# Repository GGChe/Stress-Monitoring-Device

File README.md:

# Welcome to FreeStressGame's open source Project!

Our tream provides an open-source real time embedded project based on the development of a real time biomedical device which aim is to monitor the stress level of a videogame player. This project is open source and anyone is invited to contribute freely sharing all your tips and modifications

## Table of Contents

* [Introduction](#introduction)
* [Methodology](#methodology)
* [Required Components](#required-components)
* [System Manual](#system-manual)
* [Found a Bug](#found-a-bug)
* [Contributing](#contributing)
* [Pubilcation](#publication)
* [SNS](#sns)
* [License](#lisence)

### Introduction

According to the World Health Organisation, mental disorders are a main topic in global health, specially because one in four people in the world will be affected by mental or neurological disorders at some point in their lives. It is estimated that more that 450 million people are currently suffering from such disorders, placing this risk to the top of all the ill-health's causes and disability worldwide. The main mental disorder is depression, and in many situations it is caused by stress. Nowadays, stress is a risk that every person need to face in some point of the day, like work, house, friends, etc. 

There is evidence available that supports the fact that the stress is one of the main triggers of depression. More in detail , such evidence shows that depression can stem from chronic overstimulation of the body's hypothalamic-pituitary-adrenal axis, which produces cortisol in humans. However, while adults can face the stress with therapy and different skills, children are a very enthreaten sector of the population that does not own skills against that. 

With the mentioned before, we can imagine that one of the most risky situations for a child are videogames where we set an unprepared person against a stressfull and addictive situation, causing severe damage on the child. 

Then, this project constitutes a reliable and attractive solution for parents, therapists and adults that want to monitor and control the stress status of the player.

### Methodology
#### [HeartBeat Detection]
The heartbeat measurement technology that we chose for this project is the photopletismography. 
This technique is based on the use of a photodiodethat emits a light pulse in a specific wavelength which, after passing by the blood vessel, the wavelength signal captured by the photosensor changes.  

</img>

According to that change, we can determine whether a pulse of blood has passed in a specific time, depending on our sampling rate.  

#### [Stress Recognition] 
Once the signal is taken, it is carried to the raspberry Pi using a proper wirebased connection to avoid any unwanted interaction with other signals and for a better performance of the device.  
Then, the Raspberry PI will process the data in real time and, at the same time, it will do a basic threshold based control for deciding whether the person is under stress or not. When this process recognize the stress, it makes beep sound for warning. 

### Required Components 
The device consists of the next components:
- Raspberry Pi 3 B+
- PCB adaptor: 
  * 2 X 2Kohm SMD resistors
- Wrist sensor:
  * VEML6030 Light sensor 
  * 1 X IR LED
  * 1 X 1 Kohm SMD resistor 
  * 1 X 10 Kohm SMD resistor
  * 1 X 1000 nF SMD capasitor 
- Piezo Buzzer
- RJ45 Cable
- Finger / Band type case for Wrist sensor
- Raspberry Pi case 

All circuit schematics / PCB Eagle files/ 3D Solidworks files are included in UPLOADED DOCUMENTS. 

### System Description 

#### Hardware section 
In this section you will find useful information of how to replicate our project. Given the components listed before, you need to print the pcb, which files and more deep information is shown in the PCB folder.  

</img>

* Connect PCB adaptor with Wrist sensor by RJ45 cable
* Connect PCB adaptor pins with Raspberry Pi pins as shown in below table 

<p align="center">

<p align="center">

#### Software section

##### Software setting 
To build our program in your Pi, you need to follow some steps.  

```
sudo apt-get update

git clone https://github.com/GGChe/Stress_Controller_Device
```
You would need to update and install the libraries of PHP5.6, Apache2 and compilers if your are working on a vanilla version of the OS.

```
sudo apt-get install php5.6

sudo apt-get install apache2

sudo apt-get install g++
```
If you have any problem installing php5.6 in Raspbian, cause it is not very well supported, follow this guide:
https://unnikked.ga/how-to-install-php-5-6-on-a-raspberry-pi-2-5fd93879cb14

##### Driver 
We developed a driver for the VEML6030 sensor, that uses I2C communication protocol, using the data obtained from the link below. The driver given in that project was initially prepared for Arduino but we had to modify it completely to make it run in every system using a proper c++ code.

[Mbed VEML6030 Driver](https://os.mbed.com/teams/MSS/code/VEML6030/)

##### Compilation from source

To compile the whole code, you only need to go to the code's folder and type on the terminal

```
cmake .

make 

sudo ./StressC.out
```

To run the program from the boot of the system

```
sudo nano /etc/rc.local

```

And then, write before "exit 0" the following scrypt:

```
sudo ./PATH/StressC.out

```

### Found a bug?

Bugs can be reported at: https://github.com/GGChe/Stress_Controller_Device/issues

Please try the latest release build before reporting, be sure to also include any logs or steps to reproduce you may have, as well as your Forge version, and whether or not you are using a third party loader such as Cauldron. When submitting logs please use a service such as Pastebin, do not paste the log directly into the issue.

### Contributing

Ahmed Elmogamer 
* Main role: Software Engineer 
* Specific tasks 
  : Coding the main program and making sensors' driver.  

Daewon Jung  
* Main role: Mechanical Engineer 
* Specific tasks 
  : Designing cases, assist making PCB and Promotion. 
  
Gabriel Galeote Checa 
* Main role: Electronic Engineer 
* Specific tasks 
  : Designing PCB and Website architecture development, Fabrication and Soldering of the PCB. 
  
### Publication
Check our publication in Hackaday.

### SNS 
In our socialmedia you can find some demos and video explanations of how the system works. 

Check our two youtube videos explaining how the system works!
- https://www.youtube.com/watch?v=JRjO4hhqV6E
- https://www.youtube.com/watch?v=9uvpTM_b6e0&t=2s
### Credits

This project used the current driver uploaded in mbed for other purposes, we fixed some errors for the VEML6030 use in RPI and we had to recode some sections of the driver.

We also wannt to thanks our mate Cheng who was really helpful in the lab.

### License

The MIT License

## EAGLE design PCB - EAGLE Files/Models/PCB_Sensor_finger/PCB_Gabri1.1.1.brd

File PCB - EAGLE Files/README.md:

# Electronic Design

This project consists of 2 main Printec Circuit Boards (PCB)pcbs: RPI adaptor and Sensor PCb.

The feature of the RPI adaptor pcb is to connect the correct RPI pines to the sensor circuit that we are using. We need to guide all the signal through a RJ45 cable that is going to the sensor pcb. Thus, it is need to adapt and guide signal in the correct order. 

The pcbs are shown below:
<p align="center">

<p align="center">

All the components that we are using on the PCB are Surface Mount Devices (SMD) and therefore, we should need a reflow oven to solder them, even though youu can solder everything by hang if you are skilled enough.

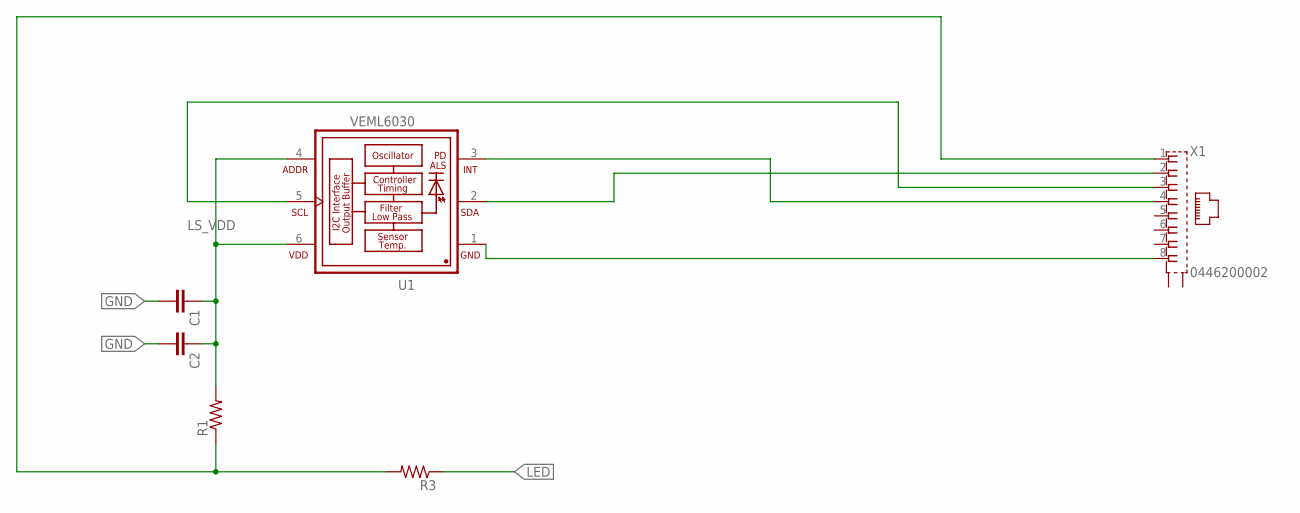
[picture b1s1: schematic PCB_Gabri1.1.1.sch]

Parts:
C1, C2: C-EU025-024X044; C025-024X044
R1, R3: R-US_R0805; R0805
U1: VEML6030; VISHAY_VEML6030_2X2X0.87
X1: 0446200002

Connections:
3V3: R1.1, R3.2, X1.1
GND: C1.2, C2.2, U1.1 (GND), X1.8
INT: U1.3 (INT), X1.4
LED: R3.1
LS_VDD: C1.1, C2.1, R1.2, U1.4 (ADDR), U1.6 (VDD)
SCL: U1.5 (SCL), X1.3
SDA: U1.2 (SDA), X1.2

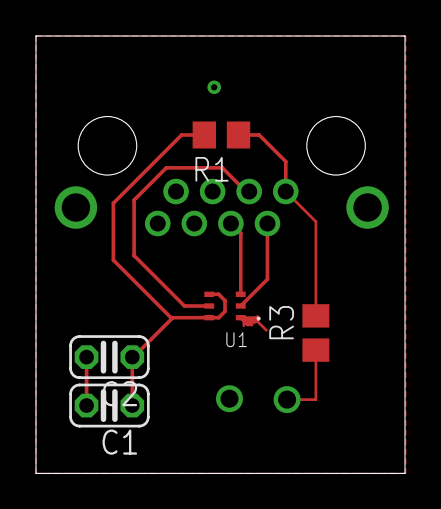
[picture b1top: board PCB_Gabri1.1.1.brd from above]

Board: 2 copper layers, 20.5 x 24.3 mm, 6 parts (1 on the bottom side), 6 nets.

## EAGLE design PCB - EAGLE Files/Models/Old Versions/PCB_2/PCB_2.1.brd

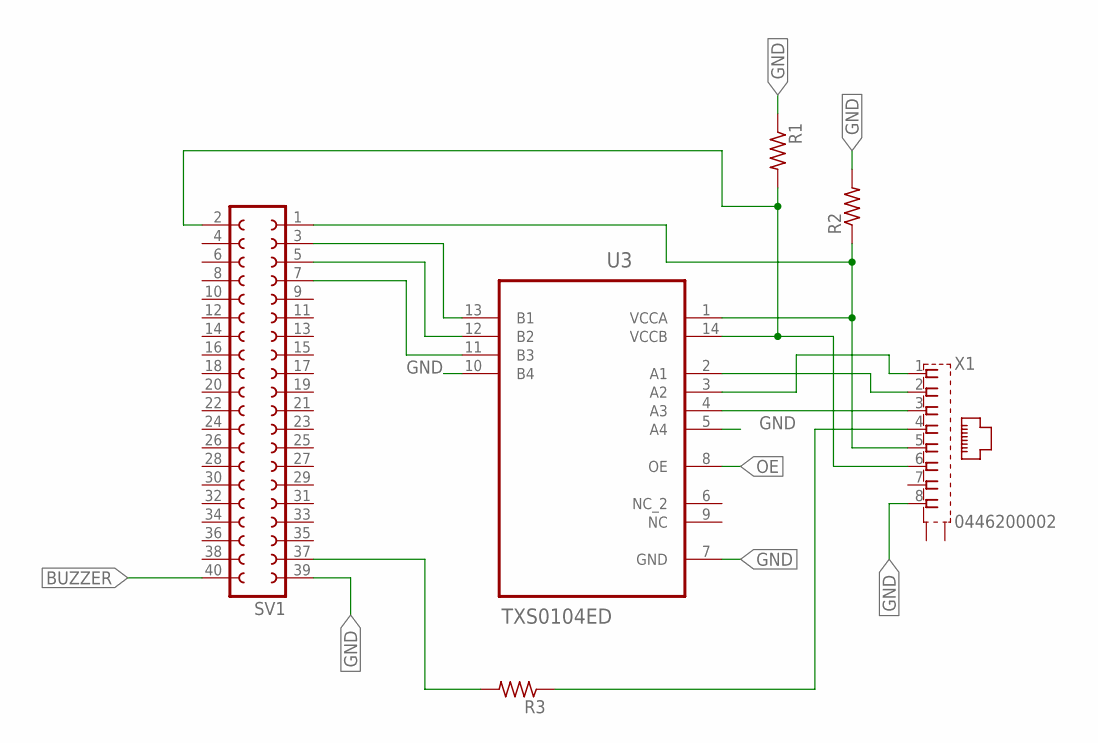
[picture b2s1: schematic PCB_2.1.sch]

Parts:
R1, R2, R3: R-US_R0805; R0805
SV1: FE20-2
U3: TXS0104ED; SOIC127P600X175-14N
X1: 0446200002

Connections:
A1: U3.2 (A1), X1.2
A2: U3.3 (A2), X1.1
A3: U3.4 (A3), X1.3
BUZZER: SV1.40
GND: R1.1, R2.2, SV1.39, U3.5 (A4), U3.7 (GND), U3.10 (B4), X1.8
INT: SV1.7, U3.11 (B3)
LED: R3.1, X1.4
unnamed: R3.2, SV1.37
OE: U3.8 (OE)
SCL: SV1.5, U3.12 (B2)
SDA: SV1.3, U3.13 (B1)
VCCA: R2.1, SV1.1, U3.1 (VCCA), X1.5
VCCB: R1.2, SV1.2, U3.14 (VCCB), X1.6

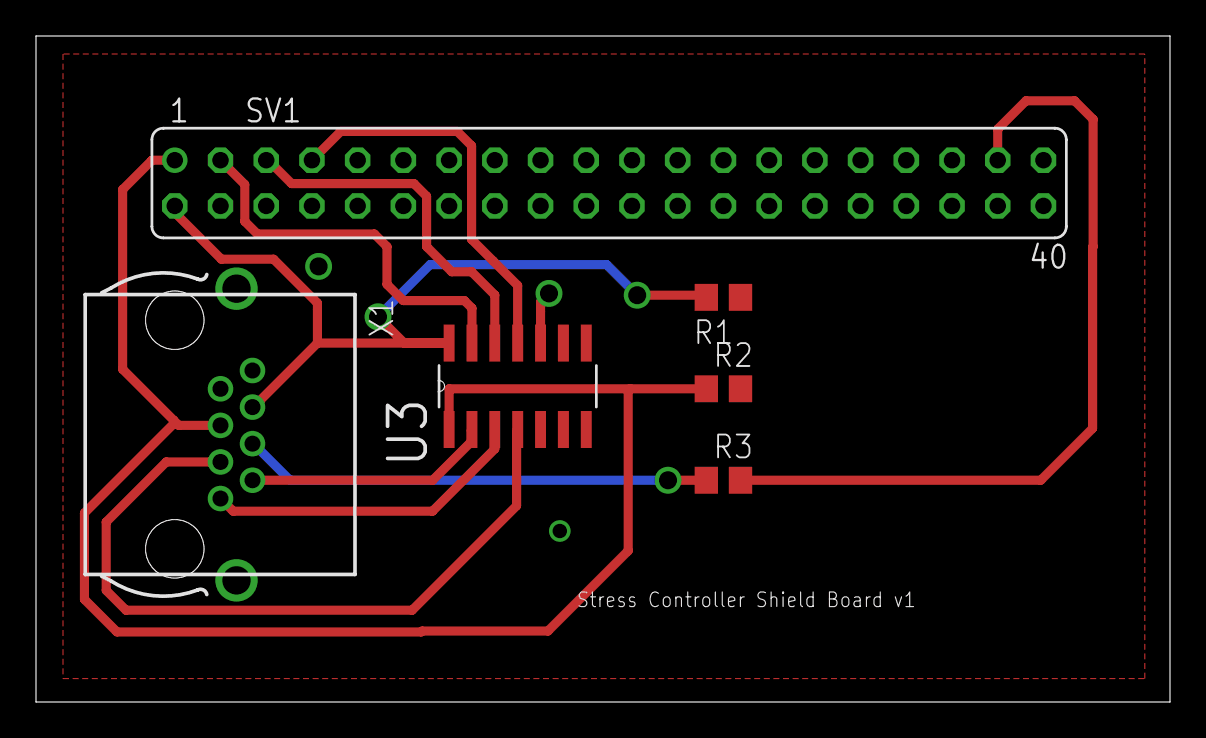
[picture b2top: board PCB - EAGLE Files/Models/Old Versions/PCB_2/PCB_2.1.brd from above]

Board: 2 copper layers, 63.0 x 37.0 mm, 6 parts (0 on the bottom side), 11 nets.

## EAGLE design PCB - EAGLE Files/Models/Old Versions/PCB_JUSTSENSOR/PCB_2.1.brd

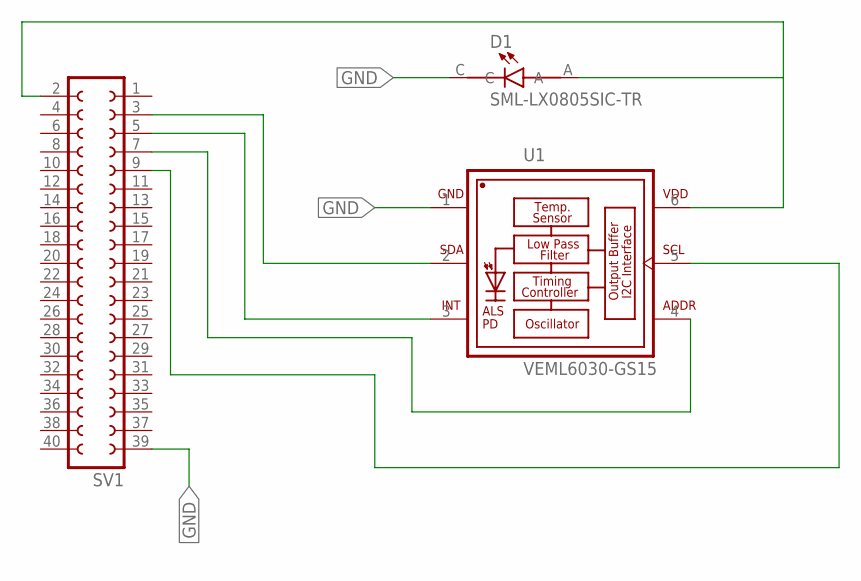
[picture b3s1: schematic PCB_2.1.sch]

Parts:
D1: SML-LX0805SIC-TR; LEDC2012X120N
SV1: FE20-2
U1: VEML6030-GS15; VISHAY_VEML6030_2X2X0.87

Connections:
GND: D1.C, SV1.39, U1.1 (GND)
unnamed: SV1.3, U1.2 (SDA)
unnamed: SV1.5, U1.3 (INT)
unnamed: SV1.9, U1.5 (SCL)
unnamed: SV1.7, U1.4 (ADDR)
VCCB: D1.A, SV1.2, U1.6 (VDD)

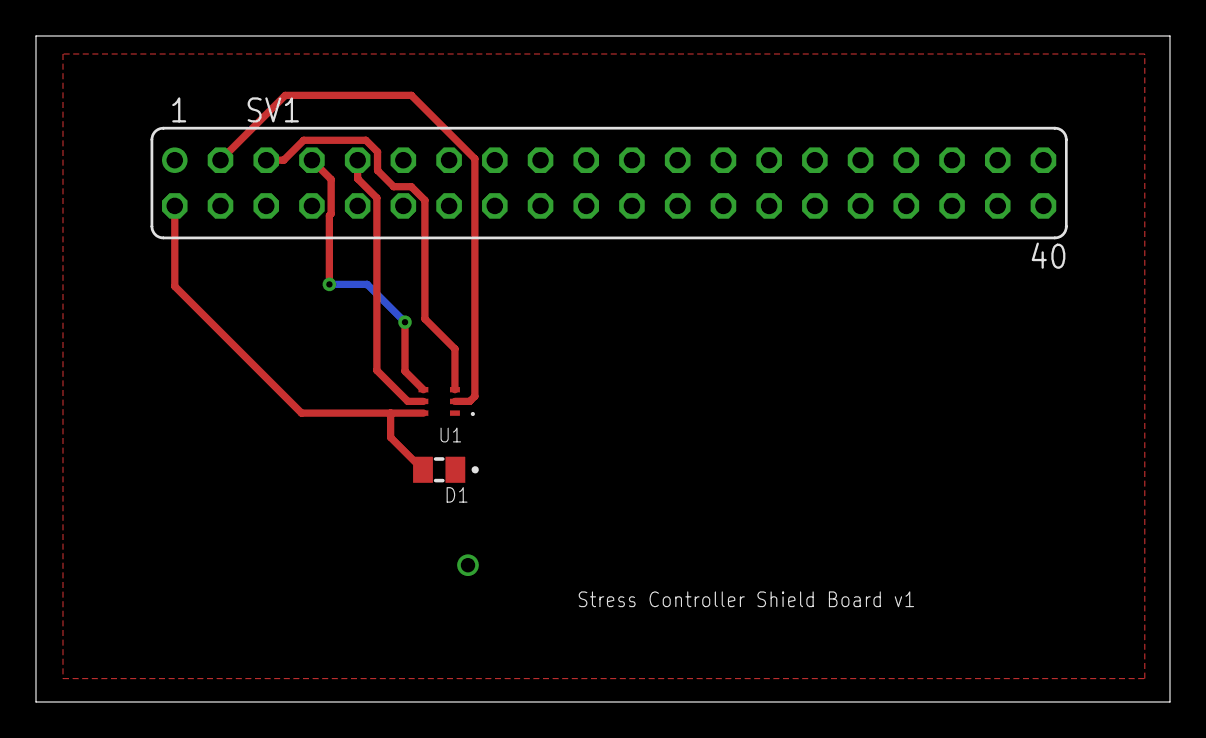
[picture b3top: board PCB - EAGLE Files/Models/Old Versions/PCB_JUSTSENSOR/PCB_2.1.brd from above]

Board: 2 copper layers, 63.0 x 37.0 mm, 3 parts (0 on the bottom side), 6 nets.

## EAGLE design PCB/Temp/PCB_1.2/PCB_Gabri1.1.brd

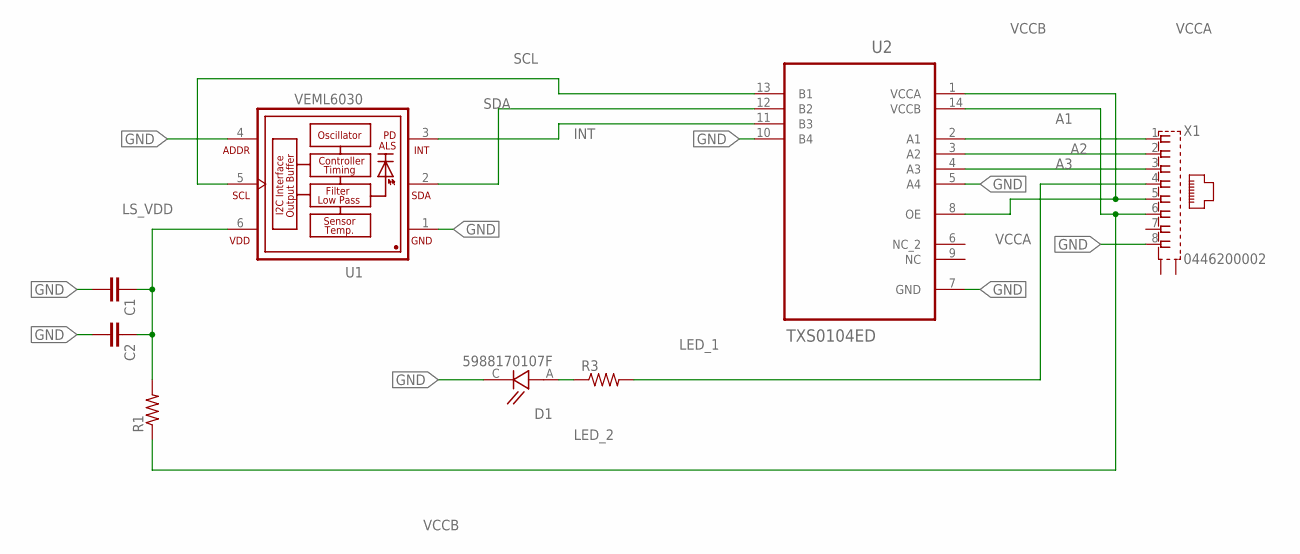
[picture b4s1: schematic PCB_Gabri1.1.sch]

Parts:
C1, C2: C-EU025-024X044; C025-024X044
D1: 5988170107F; LEDC2012X70N
R1, R3: R-US_R0805; R0805
U1: VEML6030; VISHAY_VEML6030_2X2X0.87
U2: TXS0104ED; SOIC127P600X175-14N
X1: 0446200002

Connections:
A1: U2.2 (A1), X1.1
A2: U2.3 (A2), X1.2
A3: U2.4 (A3), X1.3
GND: C1.2, C2.2, D1.C, U1.1 (GND), U1.4 (ADDR), U2.5 (A4), U2.7 (GND), U2.10 (B4), X1.8
INT: U1.3 (INT), U2.11 (B3)
LED_1: R3.2, X1.4
LED_2: D1.A, R3.1
LS_VDD: C1.1, C2.1, R1.2, U1.6 (VDD)
SCL: U1.5 (SCL), U2.13 (B1)
SDA: U1.2 (SDA), U2.12 (B2)
VCCA: U2.1 (VCCA), U2.8 (OE), X1.5
VCCB: R1.1, U2.14 (VCCB), X1.6

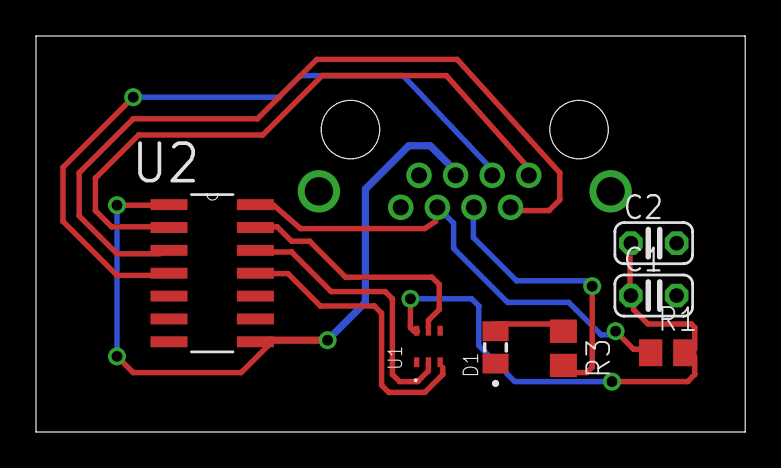
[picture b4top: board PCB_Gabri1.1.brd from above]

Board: 2 copper layers, 39.4 x 22.0 mm, 8 parts (1 on the bottom side), 12 nets.

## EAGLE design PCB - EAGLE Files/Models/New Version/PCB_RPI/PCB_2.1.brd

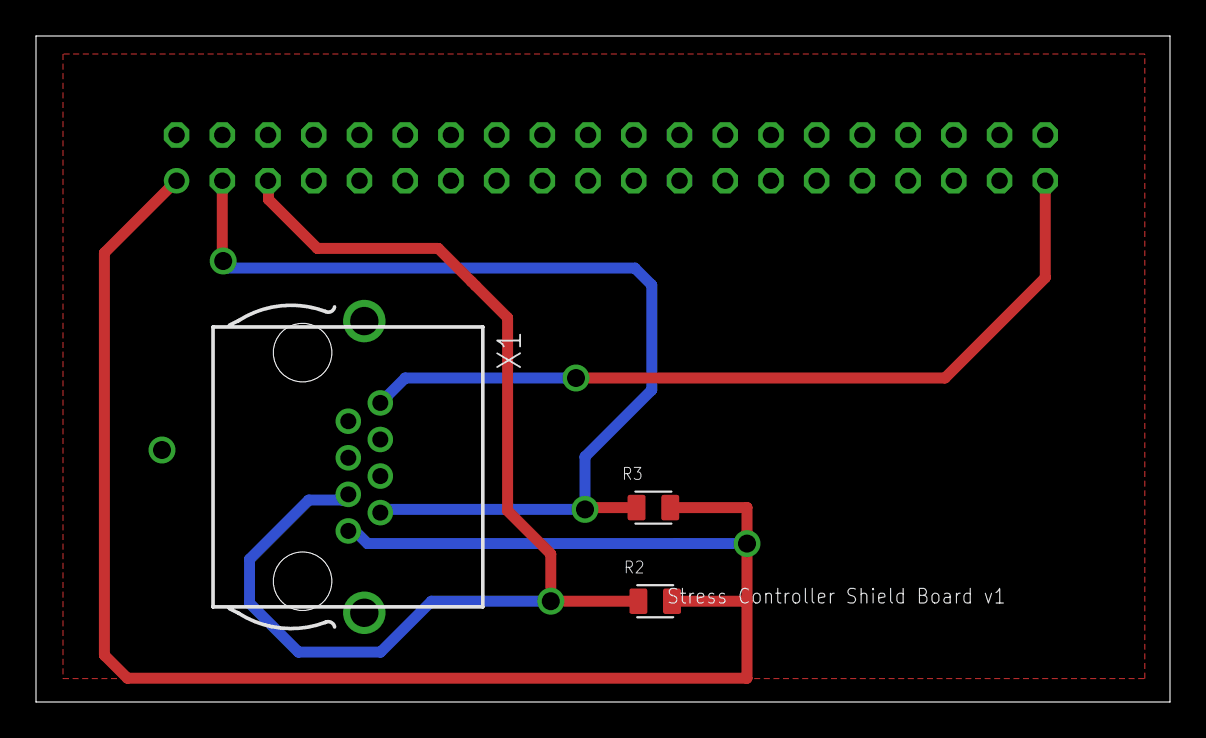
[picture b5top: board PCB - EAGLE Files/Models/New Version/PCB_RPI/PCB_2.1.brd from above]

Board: 2 copper layers, 63.0 x 37.0 mm, 4 parts (1 on the bottom side), 4 nets.

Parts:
R2, R3: TCR0805N910K; RESC2012X65N
SV1: FE20-2
X1: 0446200002

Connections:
3V3: R2.2, R3.2, SV1.1, X1.1
GND: SV1.39, X1.8
SCL: R2.1, SV1.5, X1.3
SDA: R3.1, SV1.3, X1.2

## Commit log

2019-01-16 Create Hello
2019-01-23 Create Files
2019-01-28 Create PCB DESIGN
2019-01-30 hola
2019-01-30 hello
2019-01-31 Create PCD DESIGN
2019-02-03 This is the PCB I have made, check it oiu
2019-02-04 Picture for the Report
2019-02-06 Modification of the management
2019-02-06 Create Final
2019-02-06 LAB 06022019
2019-02-09 Changes for the PCB
2019-02-10 Uploaded the ZIP of the PCB
2019-02-11 Tiding up the documents
2019-02-13 PCB drawings
2019-02-17 just a few changes
2019-02-24 Organising some documents and folders
2019-02-27 Pictures that help for the project reading and report
2019-02-28 Updating PCB printings
2019-02-28 Uploaded the final version of the PCB
2019-02-28 Create PCB case
2019-03-06 Uploading gerber files
2019-03-06 Rearrange some folders
2019-03-10 Modification of Buzzer class
2019-03-13 Uploaded thefinal printing documents of the PCB
2019-03-13 Coding
2019-03-14 Create VEMLrpi2
2019-03-15 Added a possible test for the LED
2019-03-19 ZIP folder
2019-03-20 gerber
2019-03-20 Test
2019-03-22 PCB design
2019-03-24 Final Version PCB
2019-03-24 Uploaded printings of final version pcb
2019-03-24 Document Organisation
2019-03-30 webpage
2019-03-30 Webpage update
2019-04-02 Readme
2019-04-02 Testing readme
2019-04-02 Changing Readme
2019-04-02 adding a change from the feature branch
2019-04-02 Readme modification
2019-04-05 update repository
2019-04-05 Webpage upload
2019-04-08 Doce
2019-04-09 Code
2019-04-09 Testing code
2019-04-09 white
2019-04-09 docs
2019-04-09 testing some docs
2019-04-11 Final code uploaded
2019-04-12 Code for writing and read files every second
2019-04-12 This is a coide for reading the webpage's changes over the file management
2019-04-12 Update of the code that we are already using
2019-04-14 Final Website uploaded, with a few code formatting
2019-04-14 Create LICENSE
2019-04-15 A Few Documentation changes
2019-04-15 Documentation
2019-04-15 Reorganising
2019-04-15 Files for website
